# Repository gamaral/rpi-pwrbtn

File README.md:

Raspberry Pi - PSU
==================

Formally known as Raspberry Pi Power Button (rpi-pwrbtn).

To be used in the _Marshmallow Entertainment System_, it allows the Raspberry Pi
to be powered *ON* or *OFF* from an external power button simiar to the XBOX's
own power button.

Hardware License
----------------

[CERN OPEN HARDWARE LICENSE v1.1](http://www.ohwr.org/licenses/cern-ohl/v1.1)

Disclaimer
----------

It works for me, so **USE AT YOUR OWN RISK**.

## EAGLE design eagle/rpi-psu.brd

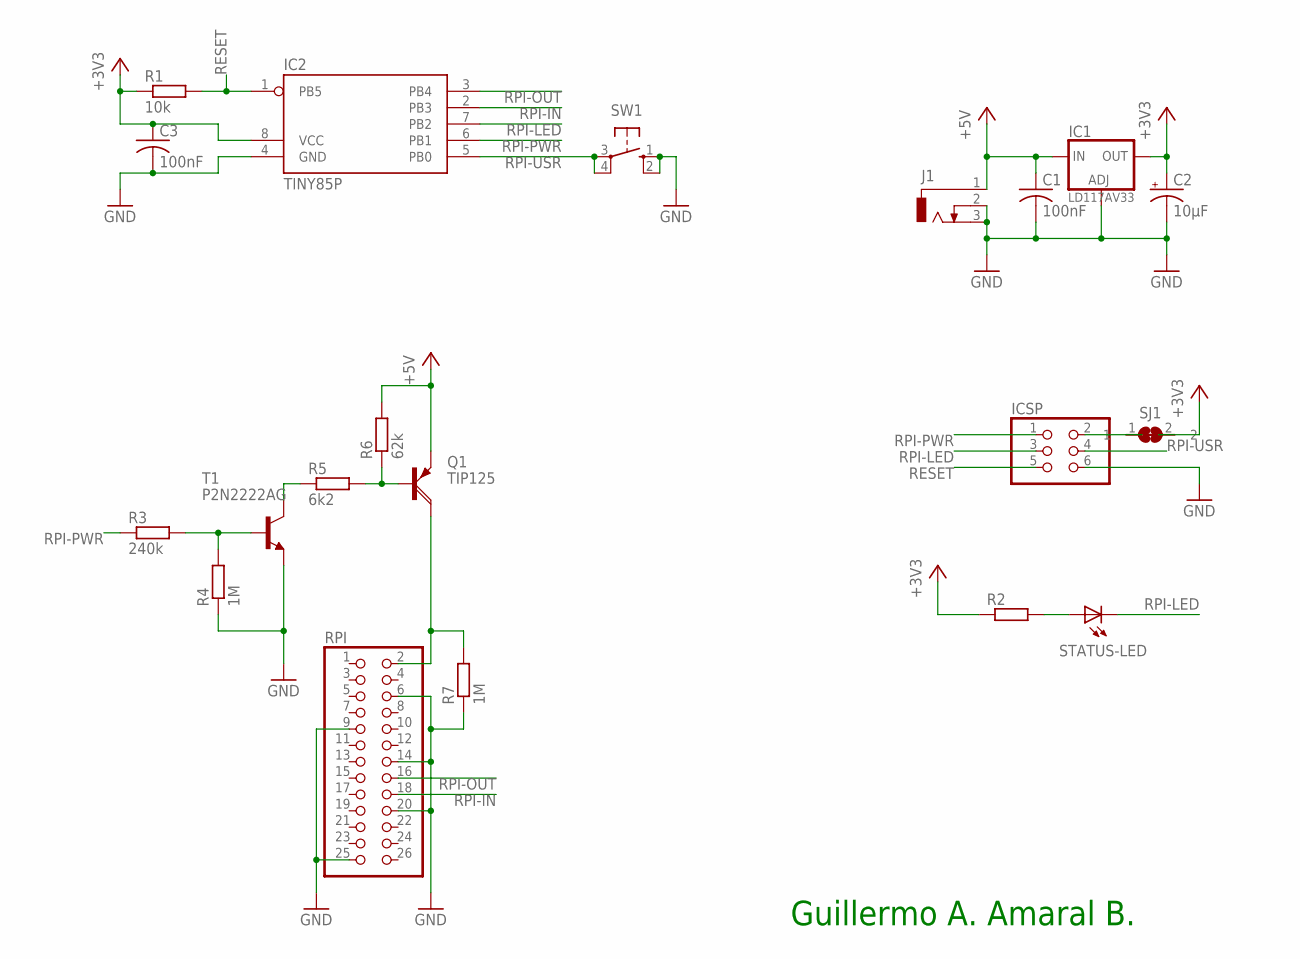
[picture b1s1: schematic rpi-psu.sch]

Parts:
C1, C3: 100nF; C050-024X044
C2: 10µF; E2,5-6E
IC1: LD117AV33; TO220L1
IC2: TINY85P; DIL08
ICSP: PINHD-2X3; 2X03
J1: DCJ0303
Q1: TIP125; TO220AH
R1: 10k; 0207/10
R2: R-EU_0207/10; 0207/10
R3: 240k; 0207/10
R4, R7: 1M; 0207/10
R5: 6k2; 0207/10
R6: 62k; 0207/10
RPI: PINHD-2X13; 2X13
SJ1: SJ-BRIDGED
STATUS-LED: LED5MM
SW1: 10-XX; B3F-10XX
T1: P2N2222AG; TO92

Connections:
+3V3: C2.+, C3.1, IC1.2 (OUT), IC2.8 (VCC), R1.1, R2.1, SJ1.2
+5V: C1.1, IC1.3 (IN), J1.1, Q1.E, R6.2
GND: C1.2, C2.-, C3.2, IC1.1 (ADJ), IC2.4 (GND), ICSP.6, J1.2, J1.3, R4.1, R7.1, RPI.6, RPI.9, RPI.14, RPI.20, RPI.25, SW1.1 (S), SW1.2 (S1), T1.3 (E)
ICSP-VCC: ICSP.2, SJ1.1
unnamed: R2.2, STATUS-LED.A
unnamed: Q1.C, R7.2, RPI.2
unnamed: Q1.B, R5.2, R6.1
unnamed: R3.2, R4.2, T1.2 (B)
unnamed: R5.1, T1.1 (C)
RESET: IC2.1 (PB5), ICSP.5, R1.2
RPI-IN: IC2.2 (PB3), RPI.18
RPI-LED: IC2.7 (PB2), ICSP.3, STATUS-LED.K (C)
RPI-OUT: IC2.3 (PB4), RPI.16
RPI-PWR: IC2.6 (PB1), ICSP.1, R3.1
RPI-USR: IC2.5 (PB0), ICSP.4, SW1.3, SW1.4 (P1)

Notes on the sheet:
Guillermo A. Amaral B.

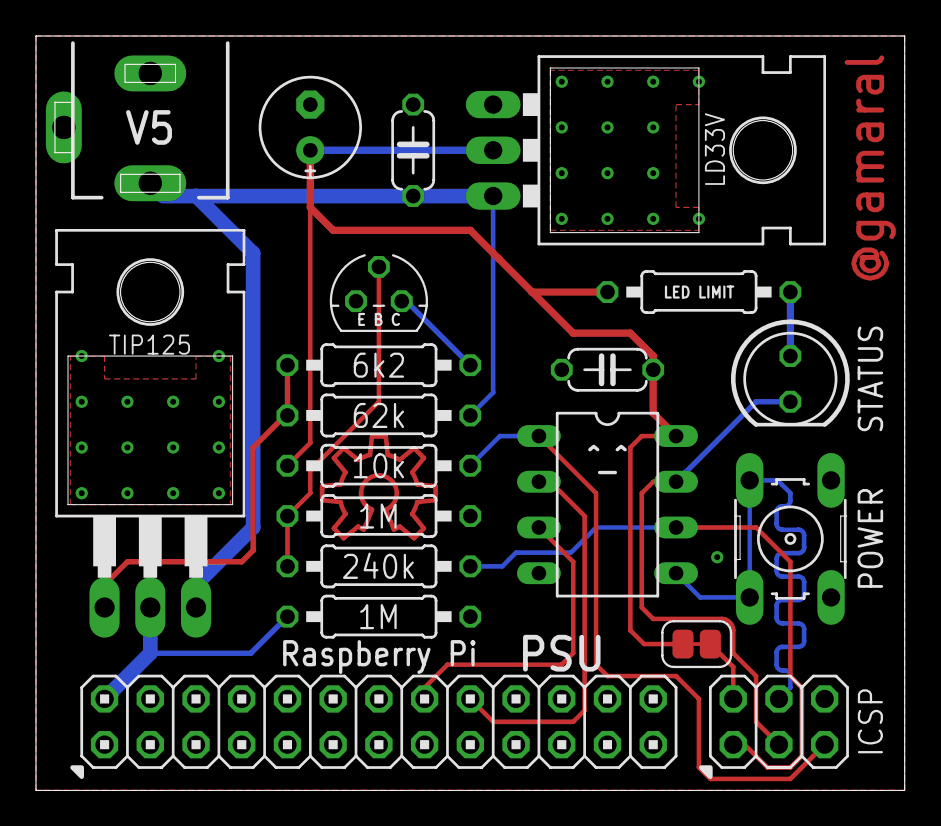
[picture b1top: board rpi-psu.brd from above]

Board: 2 copper layers, 48.3 x 41.9 mm, 20 parts (0 on the bottom side), 15 nets.

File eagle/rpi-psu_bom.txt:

Partlist exported from /home/gamaral/eagle/rpi-psu/eagle/rpi-psu.sch at 9/4/13 7:46 AM

Part       Value     Device          Package      Description                                                   
C1         100nF     C-US050-024X044 C050-024X044 CAPACITOR, American symbol                                    
C2         10µF      CPOL-USE2,5-6E  E2,5-6E      POLARIZED CAPACITOR, American symbol                          
C3         100nF     C-US050-024X044 C050-024X044 CAPACITOR, American symbol                                    
IC1        LD117AV33 LD117AV33       TO220L1      Low drop fixed and adjustable positive voltage regulators 1 A 
IC2        TINY85P   TINY85P         DIL08        AVR ATtiny85 MICROCONTROLLER                                  
ICSP                 PINHD-2X3       2X03         PIN HEADER                                                    
J1                   DCJ0303         DCJ0303      DC POWER JACK                                                 
Q1         TIP125    TIP125          TO220AH      PNP DARLINGTON TRANSISTOR                                     
R1         10k       R-EU_0207/10    0207/10      RESISTOR, European symbol                                     
R2         330R      R-EU_0207/10    0207/10      RESISTOR, European symbol                                     
R3         240k      R-EU_0207/10    0207/10      RESISTOR, European symbol                                     
R4         10k       R-EU_0207/10    0207/10      RESISTOR, European symbol                                     
R5         6k2       R-EU_0207/10    0207/10      RESISTOR, European symbol                                     
R6         62k       R-EU_0207/10    0207/10      RESISTOR, European symbol                                     
R7         10k       R-EU_0207/10    0207/10      RESISTOR, European symbol                                     
RPI                  PINHD-2X13      2X13         PIN HEADER                                                    
SJ1                  SJ-BRIDGED      SJ-BRIDGED   Solder Jumper - Bridged                                       
STATUS-LED           LED5MM          LED5MM       LED                                                           
SW1                  10-XX           B3F-10XX     OMRON SWITCH                                                  
T1         2N2222A   -NPN-TO92-EBC   TO92-EBC     NPN Transistror

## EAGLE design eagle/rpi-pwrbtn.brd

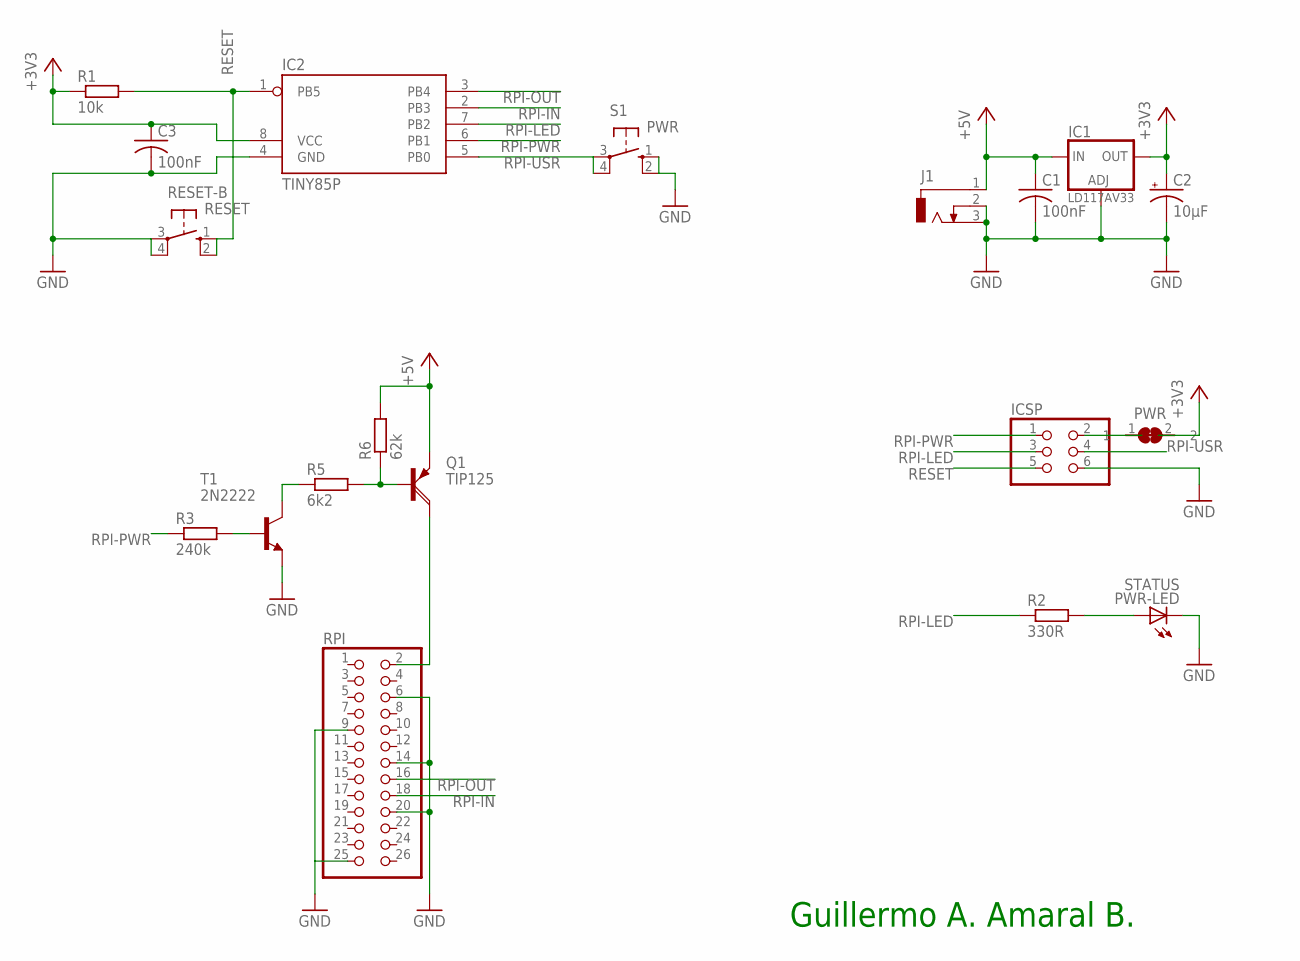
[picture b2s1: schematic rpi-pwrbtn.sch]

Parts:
C1, C3: 100nF; C050-024X044
C2: 10µF; E2,5-6E
IC1: LD117AV33; TO220L1
IC2: TINY85P; DIL08
ICSP: PINHD-2X3; 2X03
J1: DCJ0303
PWR: SJ-BRIDGED
PWR-LED: STATUS; LED5MM
Q1: TIP125; TO220AH
R1: 10k; 0204/7
R2: 330R; 0204/7
R3: 240k; 0204/7
R5: 6k2; 0204/7
R6: 62k; 0204/7
RESET-B: RESET; B3F-10XX
RPI: PINHD-2X13; 2X13
S1: PWR; B3F-10XX
T1: 2N2222; TO18

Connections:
+3V3: C2.+, C3.1, IC1.2 (OUT), IC2.8 (VCC), PWR.2, R1.1
+5V: C1.1, IC1.3 (IN), J1.1, Q1.E, R6.2
GND: C1.2, C2.-, C3.2, IC1.1 (ADJ), IC2.4 (GND), ICSP.6, J1.2, J1.3, PWR-LED.K (C), RESET-B.3, RESET-B.4 (P1), RPI.6, RPI.9, RPI.14, RPI.20, RPI.25, S1.1 (S), S1.2 (S1), T1.1 (E)
ICSP-VCC: ICSP.2, PWR.1
unnamed: PWR-LED.A, R2.2
unnamed: Q1.C, RPI.2
unnamed: Q1.B, R5.2, R6.1
unnamed: R3.2, T1.2 (B)
unnamed: R5.1, T1.3 (C)
RESET: IC2.1 (PB5), ICSP.5, R1.2, RESET-B.1 (S), RESET-B.2 (S1)
RPI-IN: IC2.2 (PB3), RPI.18
RPI-LED: IC2.7 (PB2), ICSP.3, R2.1
RPI-OUT: IC2.3 (PB4), RPI.16
RPI-PWR: IC2.6 (PB1), ICSP.1, R3.1
RPI-USR: IC2.5 (PB0), ICSP.4, S1.3, S1.4 (P1)

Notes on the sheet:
Guillermo A. Amaral B.

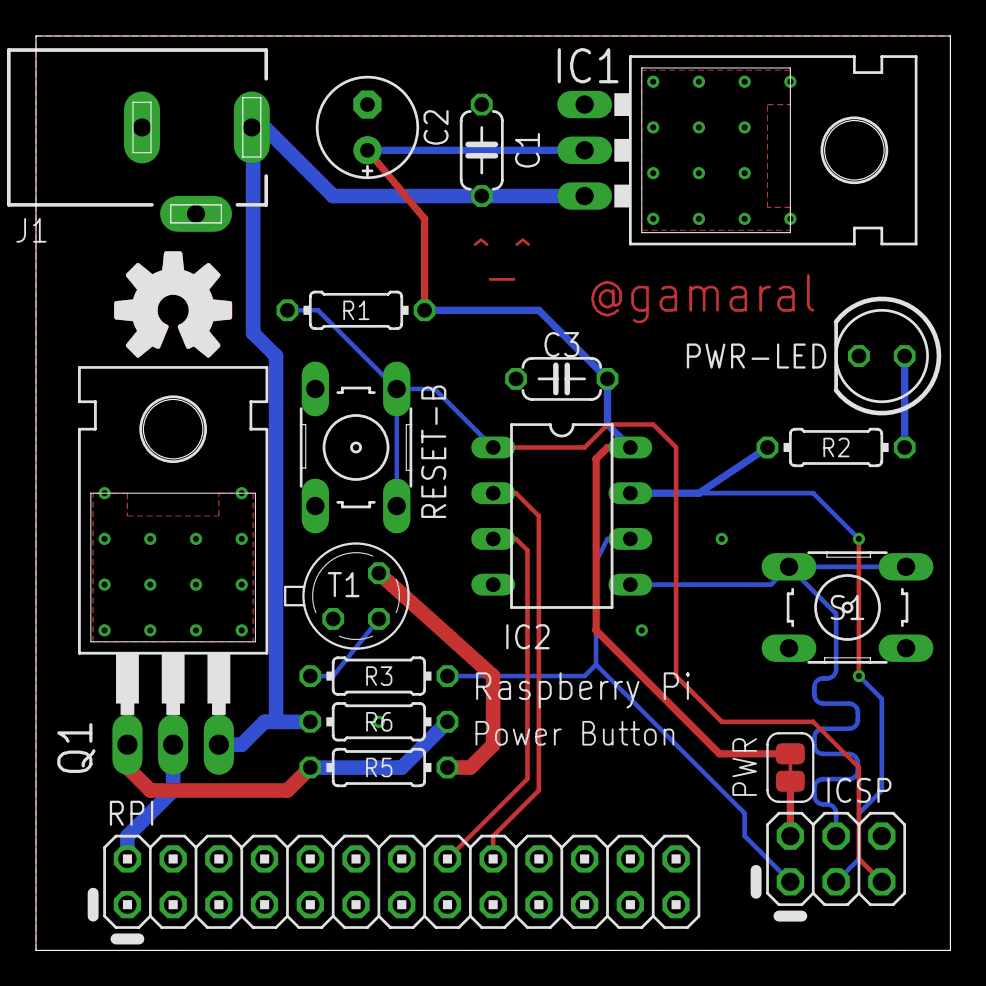
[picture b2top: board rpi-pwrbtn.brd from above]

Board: 2 copper layers, 50.8 x 50.8 mm, 19 parts (0 on the bottom side), 15 nets.

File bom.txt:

Part    Value     Device          Package
C1      100nF     C-US050-024X044 C050-024X044
C2      10µF      CPOL-USE2,5-6E  E2,5-6E
C3      100nF     C-US050-024X044 C050-024X044
IC1     LD117AV33 LD117AV33       TO220L1
IC2     TINY85P   TINY85P         DIL08
PWR-LED RED       LED5MM          LED5MM
Q1      TIP125    TIP125          TO220AH
R1      10k       R-EU_0204/7     0204/7
R2      330R      R-EU_0204/7     0204/7
R3      240k      R-EU_0204/7     0204/7
R5      6k2       R-EU_0204/7     0204/7
R6      62k       R-EU_0204/7     0204/7
RESET-B RESET     10-XX           B3F-10XX
S1      PWR       10-XX           B3F-10XX
T1      2N2222    2N2222          TO18

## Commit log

2012-09-24 Ported code to ATtiny85
2012-10-04 Add fritzing and svg schem
2013-02-22 Added eagle version (smd components, smaller, two jumpers)
2013-02-25 Reorganized directories, added eagle schematic in png
2013-08-20 Update through-hole schematic and board files.
2013-09-02 Updated to R2
2013-09-02 Removed old fritzing version.
2013-09-02 Moved bom into eagle directory.
2013-09-02 Remove old common code.
2013-09-03 Renamed project to Raspberry Pi - PSU
2013-09-04 Updated to R3.
2013-09-04 It's TIP125 not TIP127 (though you could use them interchangeably I guess)
2013-09-05 Small tweaks
2013-09-14 Updated sample client script and added rpi-buildroot based test image.
2013-09-17 R2/R3 firmware updated, Replaced NPN transistor in R3 schematic
2013-09-22 Tweaks to R3 firmware and hardware silk
2013-09-22 More silk tweaks. :)
2013-10-06 Specify hardware license
2013-10-07 Small tweaks
    Turned terminals back on for ground fills.
    LED resistor trace moved.
2013-10-07 Added gerbers
2013-11-21 Ubuntu Dash comments added to sample client script
